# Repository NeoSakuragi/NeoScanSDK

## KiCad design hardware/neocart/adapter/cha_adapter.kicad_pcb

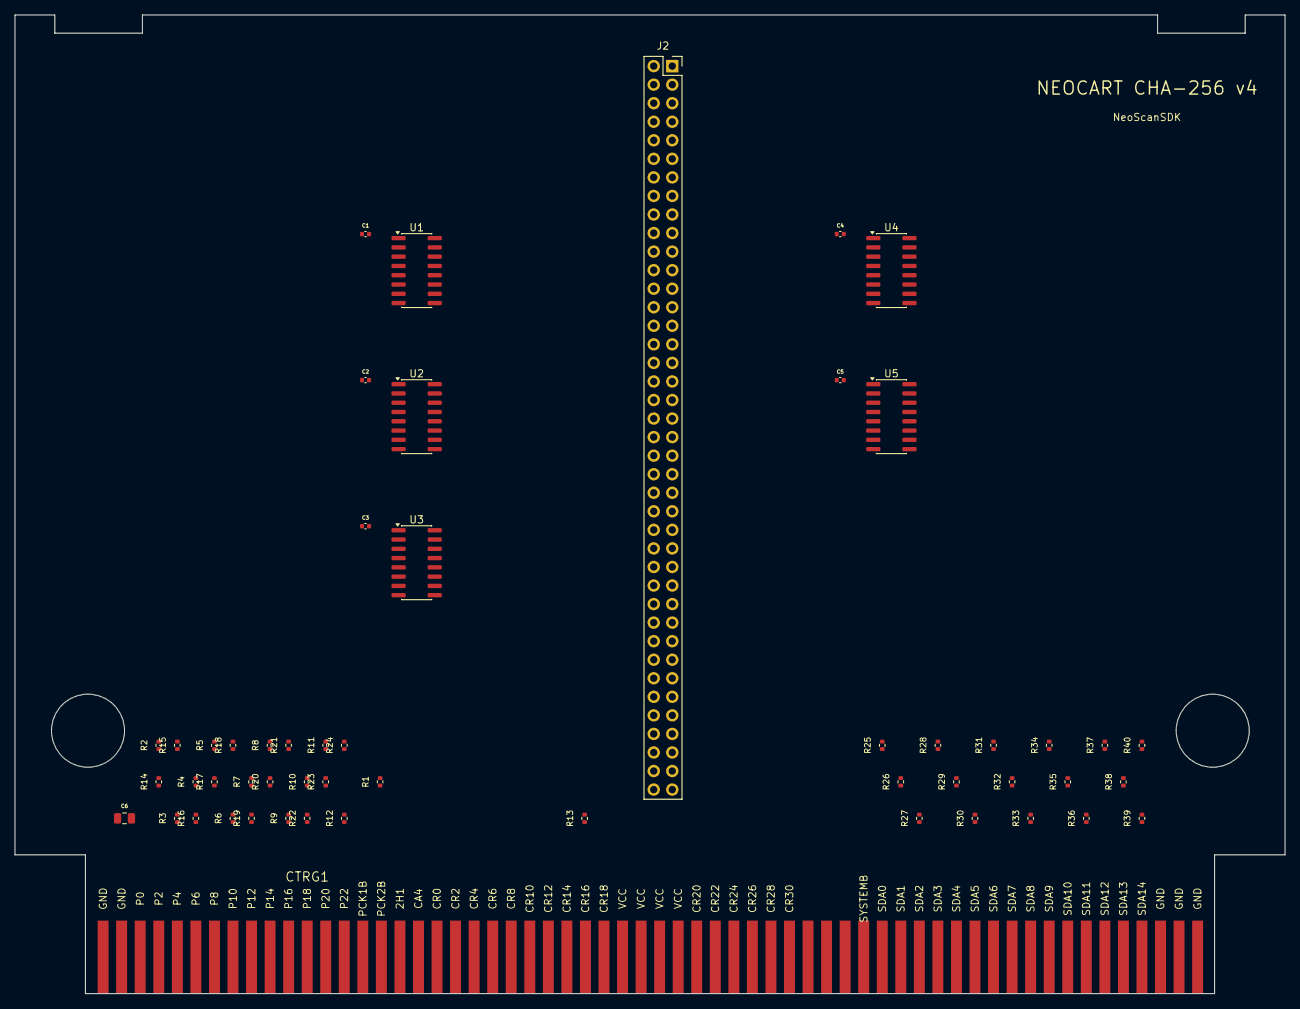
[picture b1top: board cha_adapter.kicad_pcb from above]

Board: 2 copper layers, 173.9 x 134.0 mm, 53 parts (0 on the bottom side), 151 nets, no tracks yet.

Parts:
C1, C2, C3, C4, C5: 100nF; C_0402_1005Metric
C6: 10uF; C_0805_2012Metric
CTRG1: MVS_CHA
J2: FROM_PROG; PinSocket_2x40_P2.54mm_Vertical
R1, R2, R3, R4, R5, R6, R7, R8, R9, R10, R11, R12, R13, R14, R15, R16, R17, R18, R19, R20, R21, R22, R23, R24, R25, R26, R27, R28, R29, R30, R31, R32, R33, R34, R35, R36, R37, R38, R39, R40: 470R; R_0402_1005Metric
U1, U2, U3, U4, U5: 74HC165; SOIC-16_3.9x9.9mm_P1.27mm

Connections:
CHA_CA4: CTRG1.A18, J2.69
CLK8M: CTRG1.B17, J2.67
CLK12M: CTRG1.B16, J2.66
CLK24M: CTRG1.B15, J2.65
CLK_C: J2.58, U1.2, U2.2, U3.2
CLK_S: J2.61, U4.2, U5.2
CR0: CTRG1.A19, J2.9
CR1: CTRG1.B19, J2.10
CR2: CTRG1.A20, J2.11
CR3: CTRG1.B20, J2.12
CR4: CTRG1.A21, J2.13
CR5: CTRG1.B21, J2.14
CR6: CTRG1.A22, J2.15
CR7: CTRG1.B22, J2.16
CR8: CTRG1.A23, J2.17
CR9: CTRG1.B23, J2.18
CR10: CTRG1.A24, J2.19
CR11: CTRG1.B24, J2.20
CR12: CTRG1.A25, J2.21
CR13: CTRG1.B25, J2.22
CR14: CTRG1.A26, J2.23
CR15: CTRG1.B26, J2.24
CR16: CTRG1.A27, J2.25
CR17: CTRG1.B27, J2.26
CR18: CTRG1.A28, J2.27
CR19: CTRG1.B28, J2.28
CR20: CTRG1.A33, J2.29
CR21: CTRG1.B33, J2.30
CR22: CTRG1.A34, J2.31
CR23: CTRG1.B34, J2.32
CR24: CTRG1.A35, J2.33
CR25: CTRG1.B35, J2.34
CR26: CTRG1.A36, J2.35
CR27: CTRG1.B36, J2.36
CR28: CTRG1.A37, J2.37
CR29: CTRG1.B37, J2.38
CR30: CTRG1.A38, J2.39
CR31: CTRG1.B38, J2.40
CSR1_OUT: U1.9, U2.10
CSR2_OUT: U2.9, U3.10
FIX0: CTRG1.B39, J2.49
FIX1: CTRG1.B40, J2.50
FIX2: CTRG1.B41, J2.51
FIX3: CTRG1.B42, J2.52
FIX4: CTRG1.B43, J2.53
FIX5: CTRG1.B44, J2.54
FIX6: CTRG1.B45, J2.55
FIX7: CTRG1.B46, J2.56
GND: C1.2, C2.2, C3.2, C4.2, C5.2, C6.2, CTRG1.A1, CTRG1.A2, CTRG1.A58, CTRG1.A59, CTRG1.A60, CTRG1.B1, CTRG1.B2, CTRG1.B58, CTRG1.B59, CTRG1.B60, J2.5, J2.6, J2.7, J2.8, J2.74, J2.75, J2.76, J2.77, J2.78, J2.79, J2.80, U1.8, U1.10, U1.14, U2.8, U2.14, U3.8, U3.14, U4.8, U4.10, U4.14, U5.8, U5.14
LOAD_C: J2.59, U1.1, U2.1, U3.1
LOAD_S: J2.62, U4.1, U5.1
P0: CTRG1.A3, R1.1
P0_R: R1.2, U1.7
P1: CTRG1.B3, R13.1
P1_R: R13.2, U2.3
P2: CTRG1.A4, R2.1
P2_R: R2.2, U1.6
P3: CTRG1.B4, R14.1
P3_R: R14.2, U2.13
P4: CTRG1.A5, R3.1
P4_R: R3.2, U1.5
P5: CTRG1.B5, R15.1
P5_R: R15.2, U2.12
P6: CTRG1.A6, R4.1
P6_R: R4.2, U1.4
P7: CTRG1.B6, R16.1
P7_R: R16.2, U2.11
P8: CTRG1.A7, R5.1
P8_R: R5.2, U1.3
P9: CTRG1.B7, R17.1
P9_R: R17.2, U3.7
P10: CTRG1.A8, R6.1
P10_R: R6.2, U1.13
P11: CTRG1.B8, R18.1
P11_R: R18.2, U3.6
P12: CTRG1.A9, R7.1
P12_R: R7.2, U1.12
P13: CTRG1.B9, R19.1
P13_R: R19.2, U3.5
P14: CTRG1.A10, R8.1
P14_R: R8.2, U1.11
P15: CTRG1.B10, R20.1
P15_R: R20.2, U3.4
P16: CTRG1.A11, R9.1
P16_R: R9.2, U2.7
P17: CTRG1.B11, R21.1
P17_R: R21.2, U3.3
P18: CTRG1.A12, R10.1
P18_R: R10.2, U2.6
P19: CTRG1.B12, R22.1
P19_R: R22.2, U3.13
P20: CTRG1.A13, R11.1
P20_R: R11.2, U2.5
P21: CTRG1.B13, R23.1
P21_R: R23.2, U3.12
P22: CTRG1.A14, R12.1
P22_R: R12.2, U2.4
P23: CTRG1.B14, R24.1
P23_R: R24.2, U3.11
PCK1B: CTRG1.A15, J2.63
PCK2B: CTRG1.A16, J2.64
RESET_CHA: CTRG1.B18, J2.73
SDA0: CTRG1.A43, R25.1
SDA0_R: R25.2, U4.7
SDA1: CTRG1.A44, R26.1
SDA1_R: R26.2, U4.6
SDA2: CTRG1.A45, R27.1
SDA2_R: R27.2, U4.5
SDA3: CTRG1.A46, R28.1
SDA3_R: R28.2, U4.4
SDA4: CTRG1.A47, R29.1
SDA4_R: R29.2, U4.3
SDA5: CTRG1.A48, R30.1
SDA5_R: R30.2, U4.13
SDA6: CTRG1.A49, R31.1
SDA6_R: R31.2, U4.12
SDA7: CTRG1.A50, R32.1
SDA7_R: R32.2, U4.11
SDA8: CTRG1.A51, R33.1
SDA8_R: R33.2, U5.7
SDA9: CTRG1.A52, R34.1
SDA9_R: R34.2, U5.6
SDA10: CTRG1.A53, R35.1
SDA10_R: R35.2, U5.5
SDA11: CTRG1.A54, R36.1
SDA11_R: R36.2, U5.4
SDA12: CTRG1.A55, R37.1
SDA12_R: R37.2, U5.3
SDA13: CTRG1.A56, R38.1
SDA13_R: R38.2, U5.13
SDA14: CTRG1.A57, R39.1
SDA14_R: R39.2, U5.12
SDA15: CTRG1.B57, R40.1
SDA15_R: R40.2, U5.11
SDD0: CTRG1.B48, J2.41
SDD1: CTRG1.B49, J2.42
SDD2: CTRG1.B50, J2.43
SDD3: CTRG1.B51, J2.44
SDD4: CTRG1.B52, J2.45
SDD5: CTRG1.B53, J2.46
SDD6: CTRG1.B54, J2.47
SDD7: CTRG1.B55, J2.48
SDMRD_CHA: CTRG1.B47, J2.71
SDROM: CTRG1.B56, J2.72
SER_C: J2.57, U3.9
SER_S: J2.60, U5.9
SIG_2H1: CTRG1.A17, J2.68
SSR1_OUT: U4.9, U5.10
SYSTEMB: CTRG1.A42, J2.70
VCC_3V3: J2.1, J2.2
VCC_5V: C1.1, C2.1, C3.1, C4.1, C5.1, C6.1, CTRG1.A29, CTRG1.A30, CTRG1.A31, CTRG1.A32, CTRG1.B29, CTRG1.B30, CTRG1.B31, CTRG1.B32, J2.3, J2.4, U1.16, U2.16, U3.16, U4.16, U5.16

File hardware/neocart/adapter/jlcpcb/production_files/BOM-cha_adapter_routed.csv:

Comment,Designator,Footprint,LCSC,Quantity
100nF,"C1,C2,C3,C4,C5",C_0402_1005Metric,C1525,5
10uF,C6,C_0805_2012Metric,C15850,1
470R,"R1,R10,R11,R12,R13,R14,R15,R16,R17,R18,R19,R2,R20,R21,R22,R23,R24,R25,R26,R27,R28,R29,R3,R30,R31,R32,R33,R34,R35,R36,R37,R38,R39,R4,R40,R5,R6,R7,R8,R9",R_0402_1005Metric,C25900,40
74HC165,"U1,U2,U3,U4,U5",SOIC-16_3.9x9.9mm_P1.27mm,C5613,5
FROM_PROG,J2,PinHeader_2x40_P2.54mm_Vertical,C5224034,1

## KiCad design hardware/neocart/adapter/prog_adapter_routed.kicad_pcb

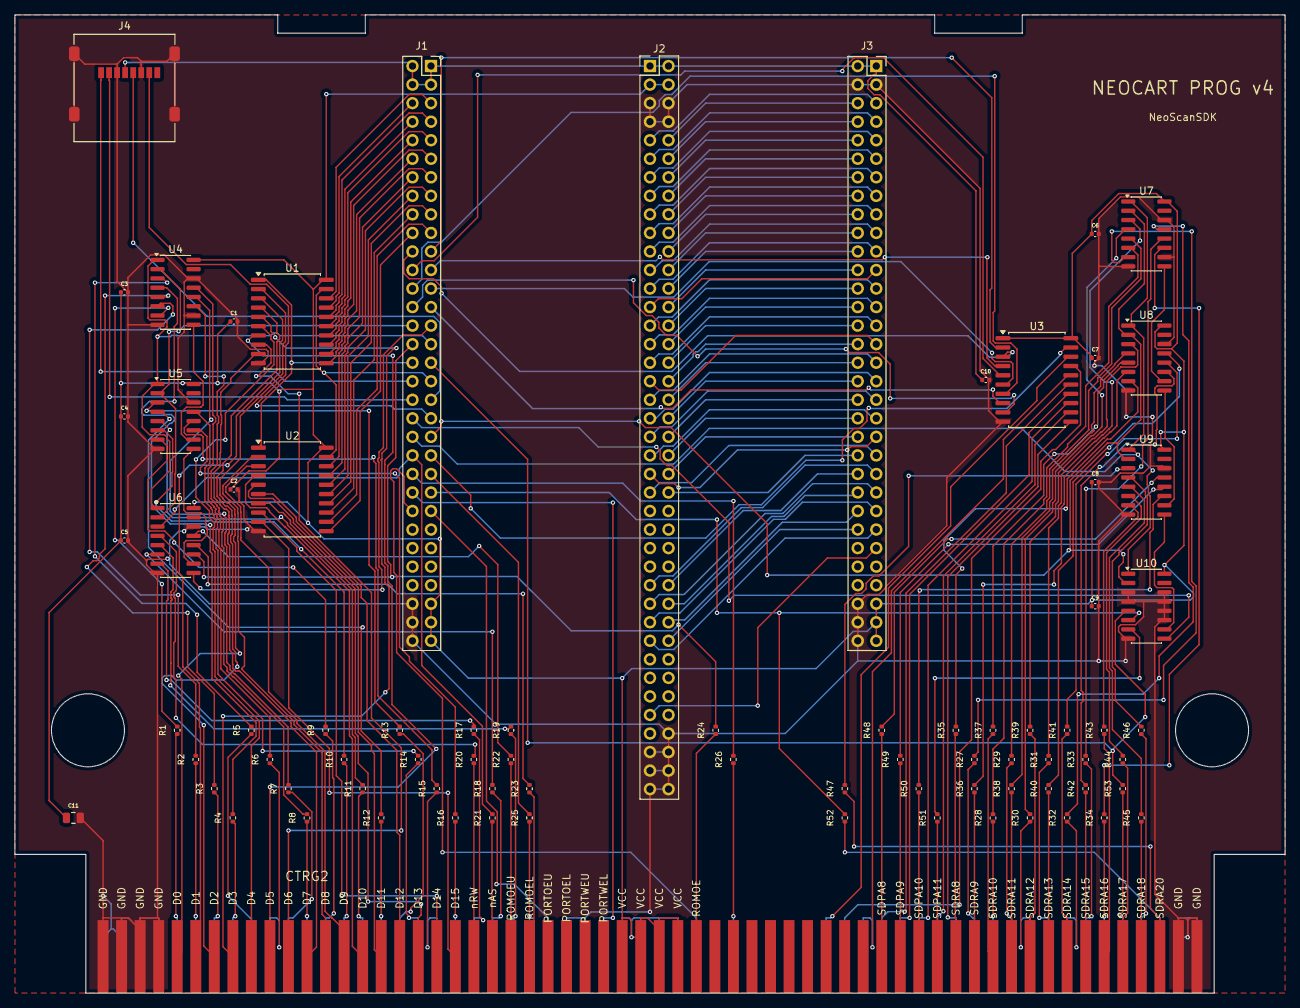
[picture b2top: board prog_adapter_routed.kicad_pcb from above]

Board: 2 copper layers, 174.0 x 134.0 mm, 79 parts (0 on the bottom side), 227 nets.

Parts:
C1, C2, C3, C4, C5, C6, C7, C8, C9, C10: 100nF; C_0402_1005Metric
C11: 10uF; C_0805_2012Metric
CTRG2: MVS_PROG
J1: FPGA_U2; PinSocket_2x32_P2.54mm_Vertical
J2: TO_CHA; PinHeader_2x40_P2.54mm_Vertical
J3: FPGA_U1; PinSocket_2x32_P2.54mm_Vertical
J4: microSD; microSD_HC_Molex_47219-2001
R1, R2, R3, R4, R5, R6, R7, R8, R9, R10, R11, R12, R13, R14, R15, R16, R17, R18, R19, R20, R21, R22, R23, R24, R25, R26, R27, R28, R29, R30, R31, R32, R33, R34, R35, R36, R37, R38, R39, R40, R41, R42, R43, R44, R45, R46, R47, R48, R49, R50, R51, R52, R53: 470R; R_0402_1005Metric
U1, U2, U3: 74LVC245; SOIC-20W_7.5x12.8mm_P1.27mm
U4, U5, U6, U7, U8, U9, U10: 74HC165; SOIC-16_3.9x9.9mm_P1.27mm

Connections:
4MB: CTRG2.B33, J1.50
68KCLK: CTRG2.B24, R25.1
68KCLK_R: J1.45, R25.2
A1: CTRG2.B5, R1.1
A1_R: R1.2, U4.7
A2: CTRG2.B6, R2.1
A2_R: R2.2, U4.6
A3: CTRG2.B7, R3.1
A3_R: R3.2, U4.5
A4: CTRG2.B8, R4.1
A4_R: R4.2, U4.4
A5: CTRG2.B9, R5.1
A5_R: R5.2, U4.3
A6: CTRG2.B10, R6.1
A6_R: R6.2, U4.13
A7: CTRG2.B11, R7.1
A7_R: R7.2, U4.12
A8: CTRG2.B12, R8.1
A8_R: R8.2, U4.11
A9: CTRG2.B13, R9.1
A9_R: R9.2, U5.7
A10: CTRG2.B14, R10.1
A10_R: R10.2, U5.6
A11: CTRG2.B15, R11.1
A11_R: R11.2, U5.5
A12: CTRG2.B16, R12.1
A12_R: R12.2, U5.4
A13: CTRG2.B17, R13.1
A13_R: R13.2, U5.3
A14: CTRG2.B18, R14.1
A14_R: R14.2, U5.13
A15: CTRG2.B19, R15.1
A15_R: R15.2, U5.12
A16: CTRG2.B20, R16.1
A16_R: R16.2, U5.11
A17: CTRG2.B21, R17.1
A17_R: R17.2, U6.7
A18: CTRG2.B22, R18.1
A18_R: R18.2, U6.6
A19: CTRG2.B23, R19.1
A19_R: R19.2, U6.5
BUF_OE: J1.35, U1.19, U2.19
BUS_DIR: J1.34, U1.1, U2.1
CLK_C: J2.58, J3.46
CLK_P: J1.30, U4.2, U5.2, U6.2
CLK_S: J2.61, J3.49
CLK_SD: J1.41, U7.2, U8.2, U9.2, U10.2
CR0: J2.9, J3.5
CR1: J2.10, J3.6
CR2: J2.11, J3.7
CR3: J2.12, J3.8
CR4: J2.13, J3.9
CR5: J2.14, J3.10
CR6: J2.15, J3.11
CR7: J2.16, J3.12
CR8: J2.17, J3.13
CR9: J2.18, J3.14
CR10: J2.19, J3.15
CR11: J2.20, J3.16
CR12: J2.21, J3.17
CR13: J2.22, J3.18
CR14: J2.23, J3.19
CR15: J2.24, J3.20
CR16: J2.25, J3.21
CR17: J2.26, J3.22
CR18: J2.27, J3.23
CR19: J2.28, J3.24
CR20: J2.29, J3.25
CR21: J2.30, J3.26
CR22: J2.31, J3.27
CR23: J2.32, J3.28
CR24: J2.33, J3.29
CR25: J2.34, J3.30
CR26: J2.35, J3.31
CR27: J2.36, J3.32
CR28: J2.37, J3.33
CR29: J2.38, J3.34
CR30: J2.39, J3.35
CR31: J2.40, J3.36
D0: CTRG2.A5, U1.2
D1: CTRG2.A6, U1.3
D2: CTRG2.A7, U1.4
D3: CTRG2.A8, U1.5
D4: CTRG2.A9, U1.6
D5: CTRG2.A10, U1.7
D6: CTRG2.A11, U1.8
D7: CTRG2.A12, U1.9
D8: CTRG2.A13, U2.2
D9: CTRG2.A14, U2.3
D10: CTRG2.A15, U2.4
D11: CTRG2.A16, U2.5
D12: CTRG2.A17, U2.6
D13: CTRG2.A18, U2.7
D14: CTRG2.A19, U2.8
D15: CTRG2.A20, U2.9
FD0: J1.5, U1.18
FD1: J1.6, U1.17
FD2: J1.7, U1.16
FD3: J1.8, U1.15
FD4: J1.9, U1.14
FD5: J1.10, U1.13
FD6: J1.11, U1.12
FD7: J1.12, U1.11
FD8: J1.13, U2.18
FD9: J1.14, U2.17
FD10: J1.15, U2.16
FD11: J1.16, U2.15
FD12: J1.17, U2.14
FD13: J1.18, U2.13
FD14: J1.19, U2.12
FD15: J1.20, U2.11
FSD0: J1.21, U3.2
FSD1: J1.22, U3.3
FSD2: J1.23, U3.4
FSD3: J1.24, U3.5
FSD4: J1.25, U3.6
FSD5: J1.26, U3.7
FSD6: J1.27, U3.8
FSD7: J1.28, U3.9
GND: C1.2, C2.2, C3.2, C4.2, C5.2, C6.2, C7.2, C8.2, C9.2, C10.2, C11.2, CTRG2.A1, CTRG2.A2, CTRG2.A3, CTRG2.A4, CTRG2.A59, CTRG2.A60, CTRG2.B1, CTRG2.B2, CTRG2.B3, CTRG2.B4, CTRG2.B26, CTRG2.B27, CTRG2.B59, CTRG2.B60, J1.60, J1.62, J1.64, J2.5, J2.6, J2.7, J2.8, J2.74, J2.75, J2.76, J2.77, J2.78, J2.79, J2.80, J3.3, J3.4, J3.60, J3.62, J3.64, J4.3, J4.6, J4.9, U1.10, U2.10, U3.10, U4.8, U4.10, U4.14, U5.8, U5.14, U6.8, U6.14, U7.8, U7.10, U7.14, U8.8, U8.14, U9.8, U9.14, U10.3, U10.4, U10.8, U10.11, U10.12, U10.13, U10.14
LOAD_C: J2.59, J3.47
LOAD_P: J1.31, U4.1, U5.1, U6.1
LOAD_S: J2.62, J3.50
LOAD_SD: J1.42, U7.1, U8.1, U9.1, U10.1
PCK1B: J2.63, J3.51
PCK2B: J2.64, J3.52
PDTACK: CTRG2.B28, J1.48
RESET: CTRG2.B35, R26.1
RESET_R: J1.46, R26.2
ROMOE: CTRG2.A33, R24.1
ROMOEL: CTRG2.A24, R23.1
ROMOEL_R: R23.2, U6.12
ROMOEU: CTRG2.A23, R22.1
ROMOEU_R: R22.2, U6.13
ROMOE_R: J1.32, R24.2, U6.11
ROMWAIT: CTRG2.B25, J1.49
SDD0: J2.41, J3.37
SDD1: J2.42, J3.38
SDD2: J2.43, J3.39
SDD3: J2.44, J3.40
SDD4: J2.45, J3.41
SDD5: J2.46, J3.42
SDD6: J2.47, J3.43
SDD7: J2.48, J3.44
SDMRD: CTRG2.B58, R52.1
SDMRD_CHA: J2.71, J3.53
SDMRD_R: J1.47, R52.2, U10.6
SDPA8: CTRG2.A43, R48.1
SDPA8_R: R48.2, U9.13
SDPA9: CTRG2.A44, R49.1
SDPA9_R: R49.2, U9.12
SDPA10: CTRG2.A45, R50.1
SDPA10_R: R50.2, U9.11
SDPA11: CTRG2.A46, R51.1
SDPA11_R: R51.2, U10.7
SDPAD0: CTRG2.B40, U3.18
SDPAD1: CTRG2.B41, U3.17
SDPAD2: CTRG2.B42, U3.16
SDPAD3: CTRG2.B43, U3.15
SDPAD4: CTRG2.B44, U3.14
SDPAD5: CTRG2.B45, U3.13
SDPAD6: CTRG2.B46, U3.12
SDPAD7: CTRG2.B47, U3.11
SDRA0: CTRG2.B48, R27.1
SDRA0_R: R27.2, U7.7
SDRA1: CTRG2.B49, R28.1
SDRA1_R: R28.2, U7.6
SDRA2: CTRG2.B50, R29.1
SDRA2_R: R29.2, U7.5
SDRA3: CTRG2.B51, R30.1
SDRA3_R: R30.2, U7.4
SDRA4: CTRG2.B52, R31.1
SDRA4_R: R31.2, U7.3
SDRA5: CTRG2.B53, R32.1
SDRA5_R: R32.2, U7.13
SDRA6: CTRG2.B54, R33.1
SDRA6_R: R33.2, U7.12
SDRA7: CTRG2.B55, R34.1
SDRA7_R: R34.2, U7.11
SDRA8: CTRG2.A47, R35.1
SDRA8_R: R35.2, U8.7
SDRA9: CTRG2.A48, R36.1
SDRA9_R: R36.2, U8.6
SDRA10: CTRG2.A49, R37.1
SDRA10_R: R37.2, U8.5
SDRA11: CTRG2.A50, R38.1
SDRA11_R: R38.2, U8.4
SDRA12: CTRG2.A51, R39.1
SDRA12_R: R39.2, U8.3
SDRA13: CTRG2.A52, R40.1
SDRA13_R: R40.2, U8.13
SDRA14: CTRG2.A53, R41.1
SDRA14_R: R41.2, U8.12
SDRA15: CTRG2.A54, R42.1
SDRA15_R: R42.2, U8.11
SDRA16: CTRG2.A55, R43.1
SDRA16_R: R43.2, U9.7
SDRA17: CTRG2.A56, R44.1
SDRA17_R: R44.2, U9.6
SDRA18: CTRG2.A57, R45.1
SDRA18_R: R45.2, U9.5
SDRA19: CTRG2.B57, R46.1
SDRA19_R: R46.2, U9.4
SDRA20: CTRG2.A58, R47.1
SDRA20_R: R47.2, U9.3
SDROE: CTRG2.B56, R53.1
SDROE_R: J1.33, R53.2, U10.5
SD_BUF_OE: J1.43, U3.19
SD_CLK: J1.37, J4.5
SD_CS: J1.36, J4.1
SD_MISO: J1.39, J4.7
SD_MOSI: J1.38, J4.2
SER_C: J2.57, J3.45
SER_P: J1.29, U6.9
SER_S: J2.60, J3.48
SER_SD: J1.40, U10.9
SR1_OUT: U4.9, U5.10
SR2_OUT: U5.9, U6.10
SSR1_OUT: U7.9, U8.10
SSR2_OUT: U8.9, U9.10
SSR3_OUT: U9.9, U10.10
VCC_3V3: C10.1, J1.1, J1.2, J1.3, J1.4, J2.1, J2.2, J3.1, J3.2, J4.4
VCC_5V: C1.1, C2.1, C3.1, C4.1, C5.1, C6.1, C7.1, C8.1, C9.1, C11.1, CTRG2.A29, CTRG2.A30, CTRG2.A31, CTRG2.A32, CTRG2.B29, CTRG2.B30, CTRG2.B31, CTRG2.B32, J1.59, J1.61, J1.63, J2.3, J2.4, J3.59, J3.61, J3.63, U1.20, U2.20, U3.1, U3.20, U4.16, U5.16, U6.16, U7.16, U8.16, U9.16, U10.16
nAS: CTRG2.A22, R21.1
nAS_R: J1.44, R21.2, U6.3
nRW: CTRG2.A21, R20.1
nRW_R: R20.2, U6.4

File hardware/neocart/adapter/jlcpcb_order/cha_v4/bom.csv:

Comment,Designator,Footprint,LCSC Part #
2x40 female socket 2.54mm 8.5mm,J2,THT,C5224034
470Ω 0402 1%,"R1,R2,R3,R4,R5,R6,R7,R8,R9,R10,R11,R12,R13,R14,R15,R16,R17,R18,R19,R20,R21,R22,R23,R24,R25,R26,R27,R28,R29,R30,R31,R32,R33,R34,R35,R36,R37,R38,R39,R40",0402,C25117
100nF 0402 16V X7R,"C1,C2,C3,C4,C5",0402,C60474
74HC165D SOIC-16,"U1,U2,U3,U4,U5",SOIC-16,C5613
10µF 0805 25V X5R,C6,0805,C15850

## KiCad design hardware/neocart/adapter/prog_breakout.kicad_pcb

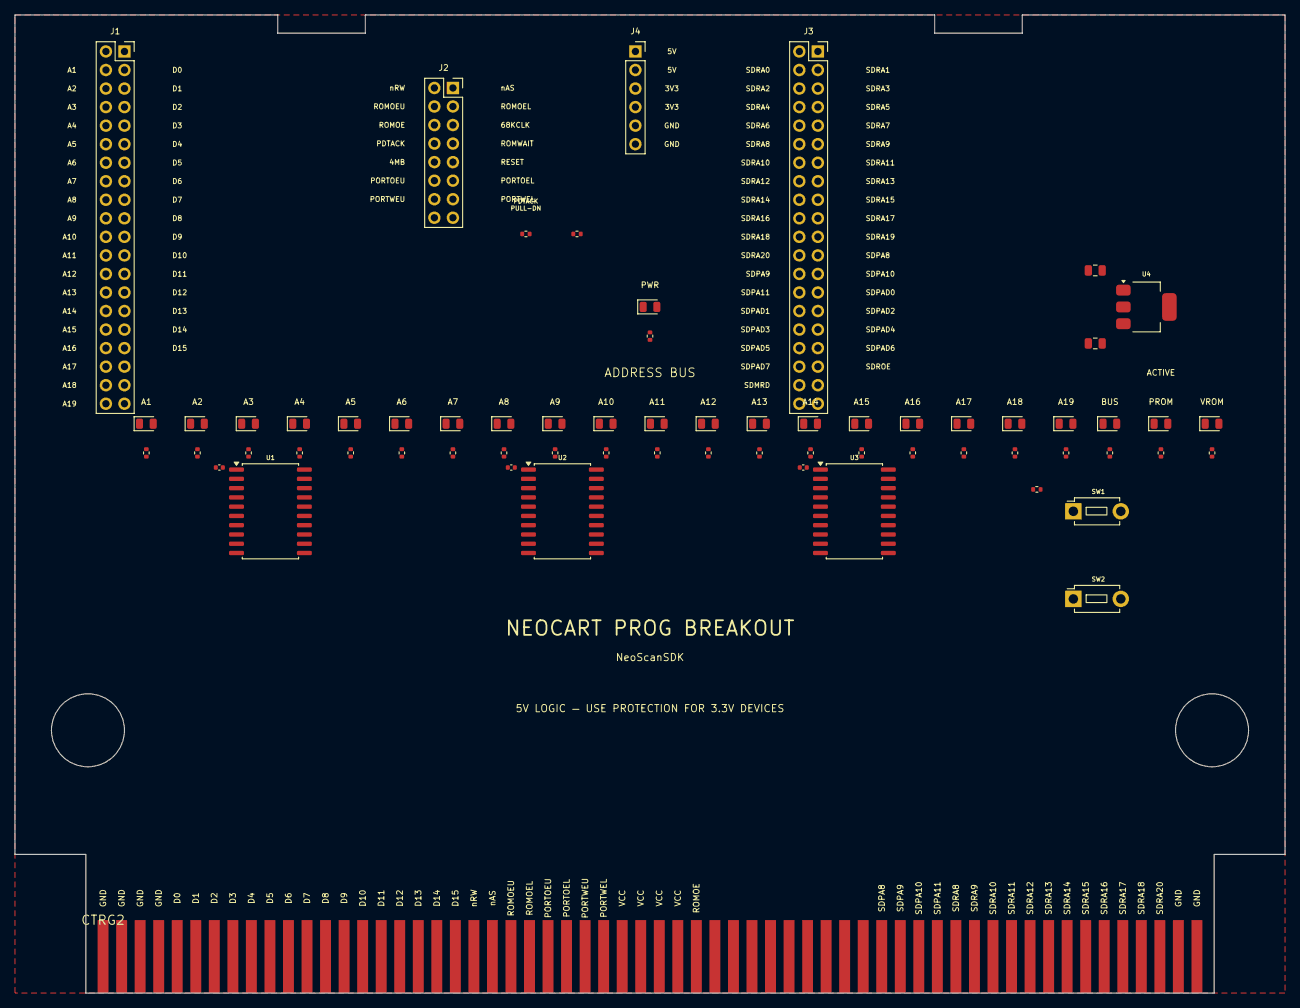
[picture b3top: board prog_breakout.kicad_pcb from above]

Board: 2 copper layers, 174.0 x 134.0 mm, 65 parts (0 on the bottom side), 130 nets, no tracks yet.

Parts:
C1, C2: 10uF; C_0805_2012Metric
C3, C4, C5: 100nF; C_0402_1005Metric
CTRG2: MVS_PROG
D1, D2, D3, D4, D5, D6, D7, D8, D9, D10, D11, D12, D13, D14, D15, D16, D17, D18, D19, D20, D21, D22: LED; LED_0805_2012Metric
D23: PWR; LED_0805_2012Metric
J1: P-ROM_BUS; PinSocket_2x20_P2.54mm_Vertical
J2: P-ROM_CTRL; PinSocket_2x08_P2.54mm_Vertical
J3: V-ROM_BUS; PinSocket_2x20_P2.54mm_Vertical
J4: POWER; PinSocket_1x06_P2.54mm_Vertical
R1, R2, R3, R4, R5, R6, R7, R8, R9, R10, R11, R12, R13, R14, R15, R16, R17, R18, R19, R20, R21, R22, R23, R25: 1K; R_0402_1005Metric
R24, R26: 10K; R_0402_1005Metric
SW1: FREEZE; SW_PUSH_1P1T_6x3.5mm_H4.3_APEM_MJTP1243
SW2: RESET; SW_PUSH_1P1T_6x3.5mm_H4.3_APEM_MJTP1243
U1, U2, U3: 74HC573; SOIC-20W_7.5x12.8mm_P1.27mm
U4: AMS1117-3.3; SOT-223-3_TabPin2

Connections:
4MB: CTRG2.B33, J2.9
68KCLK: CTRG2.B24, J2.6
A1: CTRG2.B5, J1.3, U1.2
A2: CTRG2.B6, J1.5, U1.3
A3: CTRG2.B7, J1.7, U1.4
A4: CTRG2.B8, J1.9, U1.5
A5: CTRG2.B9, J1.11, U1.6
A6: CTRG2.B10, J1.13, U1.7
A7: CTRG2.B11, J1.15, U1.8
A8: CTRG2.B12, J1.17, U1.9
A9: CTRG2.B13, J1.19, U2.2
A10: CTRG2.B14, J1.21, U2.3
A11: CTRG2.B15, J1.23, U2.4
A12: CTRG2.B16, J1.25, U2.5
A13: CTRG2.B17, J1.27, U2.6
A14: CTRG2.B18, J1.29, U2.7
A15: CTRG2.B19, J1.31, U2.8
A16: CTRG2.B20, J1.33, U2.9
A17: CTRG2.B21, J1.35, U3.2
A18: CTRG2.B22, J1.37, U3.3
A19: CTRG2.B23, J1.39, U3.4
D0: CTRG2.A5, J1.4
D1: CTRG2.A6, J1.6
D2: CTRG2.A7, J1.8
D3: CTRG2.A8, J1.10
D4: CTRG2.A9, J1.12
D5: CTRG2.A10, J1.14
D6: CTRG2.A11, J1.16
D7: CTRG2.A12, J1.18
D8: CTRG2.A13, J1.20
D9: CTRG2.A14, J1.22
D10: CTRG2.A15, J1.24
D11: CTRG2.A16, J1.26
D12: CTRG2.A17, J1.28
D13: CTRG2.A18, J1.30
D14: CTRG2.A19, J1.32
D15: CTRG2.A20, J1.34
GND: C1.2, C2.2, C3.2, C4.2, C5.2, CTRG2.A1, CTRG2.A2, CTRG2.A3, CTRG2.A4, CTRG2.A59, CTRG2.A60, CTRG2.B1, CTRG2.B2, CTRG2.B3, CTRG2.B4, CTRG2.B26, CTRG2.B27, CTRG2.B59, CTRG2.B60, J1.1, J1.38, J1.40, J2.15, J2.16, J3.1, J3.38, J3.40, J4.5, J4.6, R1.2, R2.2, R3.2, R4.2, R5.2, R6.2, R7.2, R8.2, R9.2, R10.2, R11.2, R12.2, R13.2, R14.2, R15.2, R16.2, R17.2, R18.2, R19.2, R20.2, R21.2, R22.2, R23.2, R25.2, SW1.2, SW2.2, U1.1, U1.10, U2.1, U2.10, U3.1, U3.5, U3.6, U3.7, U3.8, U3.9, U3.10, U4.1
LA1: D1.1, U1.19
LA2: D2.1, U1.18
LA3: D3.1, U1.17
LA4: D4.1, U1.16
LA5: D5.1, U1.15
LA6: D6.1, U1.14
LA7: D7.1, U1.13
LA8: D8.1, U1.12
LA9: D9.1, U2.19
LA10: D10.1, U2.18
LA11: D11.1, U2.17
LA12: D12.1, U2.16
LA13: D13.1, U2.15
LA14: D14.1, U2.14
LA15: D15.1, U2.13
LA16: D16.1, U2.12
LA17: D17.1, U3.19
LA18: D18.1, U3.18
LA19: D19.1, U3.17
LATCH_EN: R24.2, SW1.1, U1.11, U2.11, U3.11
PDTACK: CTRG2.B28, J2.7, R25.1
PORTOEL: CTRG2.A26, J2.12
PORTOEU: CTRG2.A25, J2.11
PORTWEL: CTRG2.A28, J2.14
PORTWEU: CTRG2.A27, J2.13
RACT_ROMOEU: D21.2, R21.1
RACT_SDROE: D22.2, R22.1
RACT_nAS: D20.2, R20.1
RESET: CTRG2.B35, J2.10, SW2.1
RLED1: D1.2, R1.1
RLED2: D2.2, R2.1
RLED3: D3.2, R3.1
RLED4: D4.2, R4.1
RLED5: D5.2, R5.1
RLED6: D6.2, R6.1
RLED7: D7.2, R7.1
RLED8: D8.2, R8.1
RLED9: D9.2, R9.1
RLED10: D10.2, R10.1
RLED11: D11.2, R11.1
RLED12: D12.2, R12.1
RLED13: D13.2, R13.1
RLED14: D14.2, R14.1
RLED15: D15.2, R15.1
RLED16: D16.2, R16.1
RLED17: D17.2, R17.1
RLED18: D18.2, R18.1
RLED19: D19.2, R19.1
ROMOE: CTRG2.A33, J2.5
ROMOEL: CTRG2.A24, J2.4
ROMOEU: CTRG2.A23, D21.1, J2.3
ROMWAIT: CTRG2.B25, J2.8, R26.2
RPWR: D23.2, R23.1
SDMRD: CTRG2.B58, J3.37
SDPA8: CTRG2.A43, J3.24
SDPA9: CTRG2.A44, J3.25
SDPA10: CTRG2.A45, J3.26
SDPA11: CTRG2.A46, J3.27
SDPAD0: CTRG2.B40, J3.28
SDPAD1: CTRG2.B41, J3.29
SDPAD2: CTRG2.B42, J3.30
SDPAD3: CTRG2.B43, J3.31
SDPAD4: CTRG2.B44, J3.32
SDPAD5: CTRG2.B45, J3.33
SDPAD6: CTRG2.B46, J3.34
SDPAD7: CTRG2.B47, J3.35
SDRA0: CTRG2.B48, J3.3
SDRA1: CTRG2.B49, J3.4
SDRA2: CTRG2.B50, J3.5
SDRA3: CTRG2.B51, J3.6
SDRA4: CTRG2.B52, J3.7
SDRA5: CTRG2.B53, J3.8
SDRA6: CTRG2.B54, J3.9
SDRA7: CTRG2.B55, J3.10
SDRA8: CTRG2.A47, J3.11
SDRA9: CTRG2.A48, J3.12
SDRA10: CTRG2.A49, J3.13
SDRA11: CTRG2.A50, J3.14
SDRA12: CTRG2.A51, J3.15
SDRA13: CTRG2.A52, J3.16
SDRA14: CTRG2.A53, J3.17
SDRA15: CTRG2.A54, J3.18
SDRA16: CTRG2.A55, J3.19
SDRA17: CTRG2.A56, J3.20
SDRA18: CTRG2.A57, J3.21
SDRA19: CTRG2.B57, J3.22
SDRA20: CTRG2.A58, J3.23
SDROE: CTRG2.B56, D22.1, J3.36
VCC: C1.1, C3.1, C4.1, C5.1, CTRG2.A29, CTRG2.A30, CTRG2.A31, CTRG2.A32, CTRG2.B29, CTRG2.B30, CTRG2.B31, CTRG2.B32, D23.1, J1.2, J3.2, J4.1, J4.2, R24.1, R26.1, U1.20, U2.20, U3.20, U4.3
VCC_3V3: C2.1, J1.36, J3.39, J4.3, J4.4, U4.2
nAS: CTRG2.A22, D20.1, J2.2
nRW: CTRG2.A21, J2.1

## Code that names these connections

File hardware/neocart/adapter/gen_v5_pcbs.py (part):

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for i in range(19):
    prog_resistors.append((f'R{ri}', GF_X(i+5), f'A{i+1}', f'A{i+1}_R')); ri += 1
# Control
for pin, sig in [(21,'nRW'),(22,'nAS'),(23,'ROMOEU'),(24,'ROMOEL'),(33,'ROMOE')]:
    prog_resistors.append((f'R{ri}', GF_X(pin), sig, f'{sig}_R')); ri += 1
# Direct
for pin, sig in [(24,'68KCLK'),(35,'RESET')]:
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    prog_resistors.append((f'R{ri}', GF_X(48+i), f'SDRA{i}', f'SDRA{i}_R')); ri += 1
for i in range(8,18):
    prog_resistors.append((f'R{ri}', GF_X(47+i-8), f'SDRA{i}', f'SDRA{i}_R')); ri += 1
prog_resistors.append((f'R{ri}', GF_X(57), 'SDRA18', 'SDRA18_R')); ri += 1
prog_resistors.append((f'R{ri}', GF_X(57), 'SDRA19', 'SDRA19_R')); ri += 1
prog_resistors.append((f'R{ri}', GF_X(58), 'SDRA20', 'SDRA20_R')); ri += 1
for i in range(4):
    prog_resistors.append((f'R{ri}', GF_X(43+i), f'SDPA{i+8}', f'SDPA{i+8}_R')); ri += 1
prog_resistors.append((f'R{ri}', GF_X(58), 'SDMRD', 'SDMRD_R')); ri += 1
prog_resistors.append((f'R{ri}', GF_X(56), 'SDROE', 'SDROE_R')); ri += 1
print(f"  {ri-1} resistors on PROG")

# Exclusion zones for resistors
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    cha_resistors.append((f'R{ri}', GF_X(i+3), f'P{i*2+1}', f'P{i*2+1}_R')); ri += 1
for i in range(15):
    cha_resistors.append((f'R{ri}', GF_X(43+i), f'SDA{i}', f'SDA{i}_R')); ri += 1
cha_resistors.append((f'R{ri}', GF_X(57), 'SDA15', 'SDA15_R')); ri += 1
print(f"  {ri-1} resistors on CHA")

def cha_rx_excluded(rx):
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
